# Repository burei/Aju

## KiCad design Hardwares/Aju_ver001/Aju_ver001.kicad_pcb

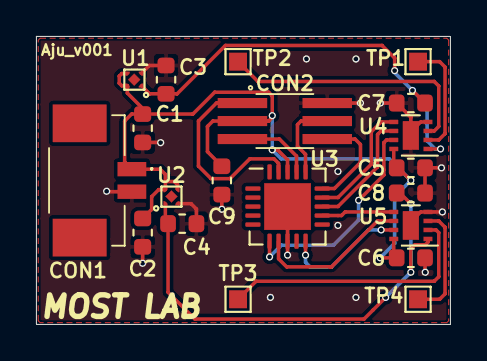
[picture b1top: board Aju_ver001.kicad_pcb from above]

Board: 2 copper layers, 23.0 x 16.0 mm, 20 parts (0 on the bottom side), 18 nets.

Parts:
C1, C2, C3, C4, C9: 0.1uF; C1608
C5, C6, C7, C8: 0.1 uF; C1608
CON1: 53261-0271; 532610271
CON2: FTM-103-02-F-DV; FTM-103-XX-Y-DV
TP1: MOUT_11; TestPoint_Pad_1.0x1.0mm
TP2: MOUT_12; TestPoint_Pad_1.0x1.0mm
TP3: MOUT_21; TestPoint_Pad_1.0x1.0mm
TP4: MOUT_22; TestPoint_Pad_1.0x1.0mm
U1: RP110L251D-TR; RP110x-DFN1010-4
U2: RP110L301D-TR; RP110x-DFN1010-4
U3: ATtiny2313A-MU; MLF-20-1EP_4x4mm_P0.5mm_EP2.6x2.6mm
U4, U5: DRV8837; WSON-8-1EP_2x2mm_P0.5mm_EP0.9x1.6mm

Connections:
+2V5: C3.1, C7.1, U1.1, U4.1
+3V0: C4.1, C8.1, U2.1, U5.1
+BATT: C1.1, C2.1, C5.1, C6.1, C9.1, CON1.1, CON2.3, U1.3, U1.4, U2.3, U2.4, U3.18, U4.8, U5.8
/02. MCU/MISO: CON2.4, U3.16
/02. MCU/MOSI: CON2.6, U3.15
/02. MCU/RST: CON2.1, U3.19
/02. MCU/SCK: CON2.5, U3.17
/03. Driver/MOUT_11: TP1.1, U4.2
/03. Driver/MOUT_12: TP2.1, U4.3
/03. Driver/MOUT_21: TP3.1, U5.2
/03. Driver/MOUT_22: TP4.1, U5.3
D1: U3.6, U4.7
D2: U3.10, U5.7
GND: C1.2, C2.2, C3.2, C4.2, C5.2, C6.2, C7.2, C8.2, C9.2, CON1.2, CON2.2, U1.2, U2.2, U3.8, U3.21, U4.4, U4.9, U5.4, U5.9
PWM1: U3.14, U4.5
PWM2: U3.13, U4.6
PWM3: U3.12, U5.5
PWM4: U3.7, U5.6

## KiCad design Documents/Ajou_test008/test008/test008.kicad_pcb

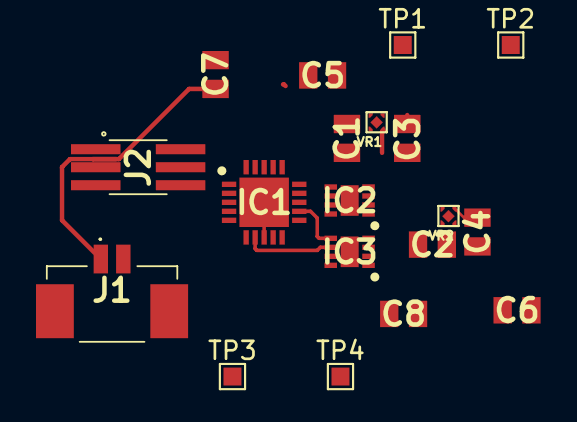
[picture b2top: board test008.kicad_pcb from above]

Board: 2 copper layers, 19 parts (0 on the bottom side), 18 nets.

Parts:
C1, C2, C3, C4, C5, C6, C7, C8: C0805C104K5RACTU; CAPC2012X88N
IC1: ATTINY2313A-MU; QFN50P400X400X80-21N-D
IC2, IC3: DRV8837DSGR; SON50P200X200X80-9N
J1: 53261-0271; 532610271
J2: FTM-103-02-F-DV; FTM-103-XX-Y-DV
TP1, TP2, TP3, TP4: TestPoint; TestPoint_Pad_1.0x1.0mm
VR1, VR2: RP110x; RP110x-DFN1010-4

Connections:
unnamed: C1.1, C2.1, C3.1, C4.1, C5.1, C6.1, C7.1, C8.1, IC1.8, IC1.21, IC2.4, IC2.9, IC3.4, IC3.9, J1.2, J1.MP1, J1.MP2, J2.2, VR1.2, VR2.2
unnamed: C1.2, C2.2, C7.2, C8.2, IC1.18, IC2.8, IC3.8, J1.1, J2.3, VR1.4, VR2.4
unnamed: C3.2, C5.2, IC2.1, VR1.1
unnamed: C4.2, C6.2, IC3.1, VR2.1
unnamed: IC1.7, IC3.6
unnamed: IC1.10, IC3.7
unnamed: IC1.11, IC2.7
unnamed: IC1.12, IC3.5
unnamed: IC1.13, IC2.6
unnamed: IC1.14, IC2.5
unnamed: IC1.15, J2.4
unnamed: IC1.16, J2.6
unnamed: IC1.17, J2.5
unnamed: IC1.19, J2.1
unnamed: IC2.2, TP2.1
unnamed: IC2.3, TP1.1
unnamed: IC3.2, TP3.1
unnamed: IC3.3, TP4.1
